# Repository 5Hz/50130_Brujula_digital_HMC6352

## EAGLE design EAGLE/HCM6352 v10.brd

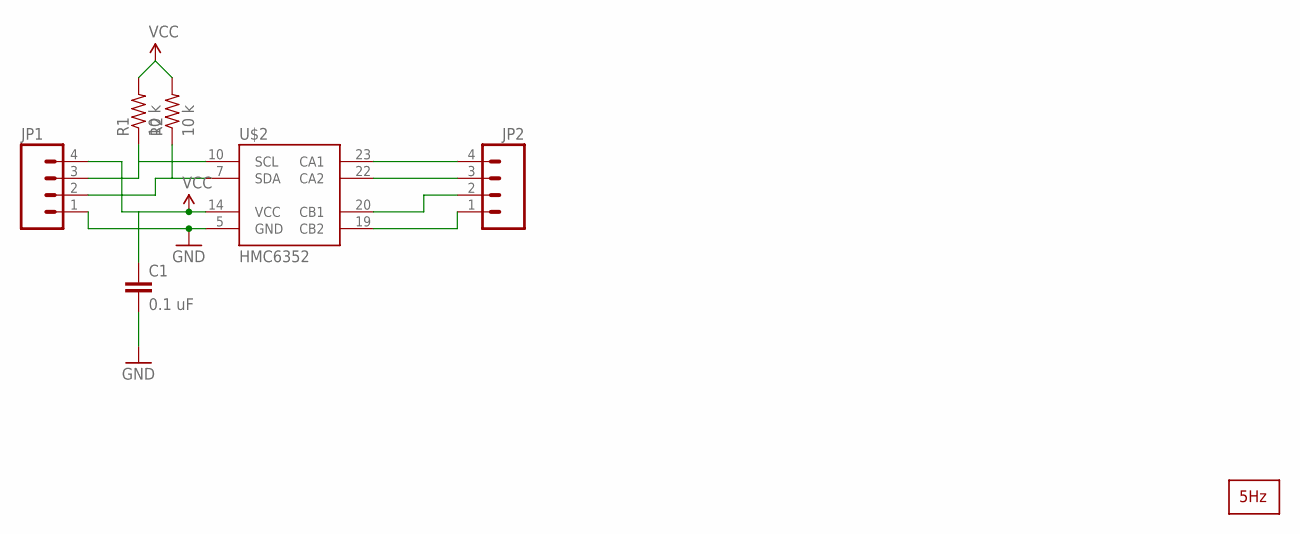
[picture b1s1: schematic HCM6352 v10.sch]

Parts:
C1: 0.1 uF; 0603-CAP
JP1, JP2: M04PTH; 1X04
R1, R2: 10 k; 0603-RES
U$1: LOGO2_SILK5MM; LOGO2_5MM
U$2: HMC6352; LCC24

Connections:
GND: C1.2, JP1.1, U$2.5 (GND)
unnamed: JP1.3, R1.1, U$2.10 (SCL)
unnamed: JP1.2, R2.1, U$2.7 (SDA)
unnamed: JP2.4, U$2.23 (CA1)
unnamed: JP2.3, U$2.22 (CA2)
unnamed: JP2.2, U$2.20 (CB1)
unnamed: JP2.1, U$2.19 (CB2)
VCC: C1.1, JP1.4, R1.2, R2.2, U$2.14 (VCC)

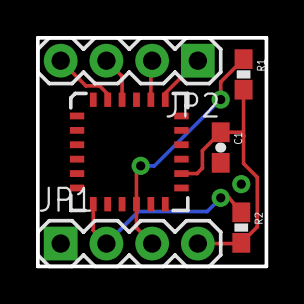
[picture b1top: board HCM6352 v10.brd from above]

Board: 2 copper layers, 12.7 x 12.7 mm, 7 parts (1 on the bottom side), 8 nets.

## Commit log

2014-01-14 creación
2014-02-04 Actualizar código

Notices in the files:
parts and their libraries:
SparkFun: Licensing: CC v3.0 Share-Alike You are welcome to use this library for commercial purposes.
